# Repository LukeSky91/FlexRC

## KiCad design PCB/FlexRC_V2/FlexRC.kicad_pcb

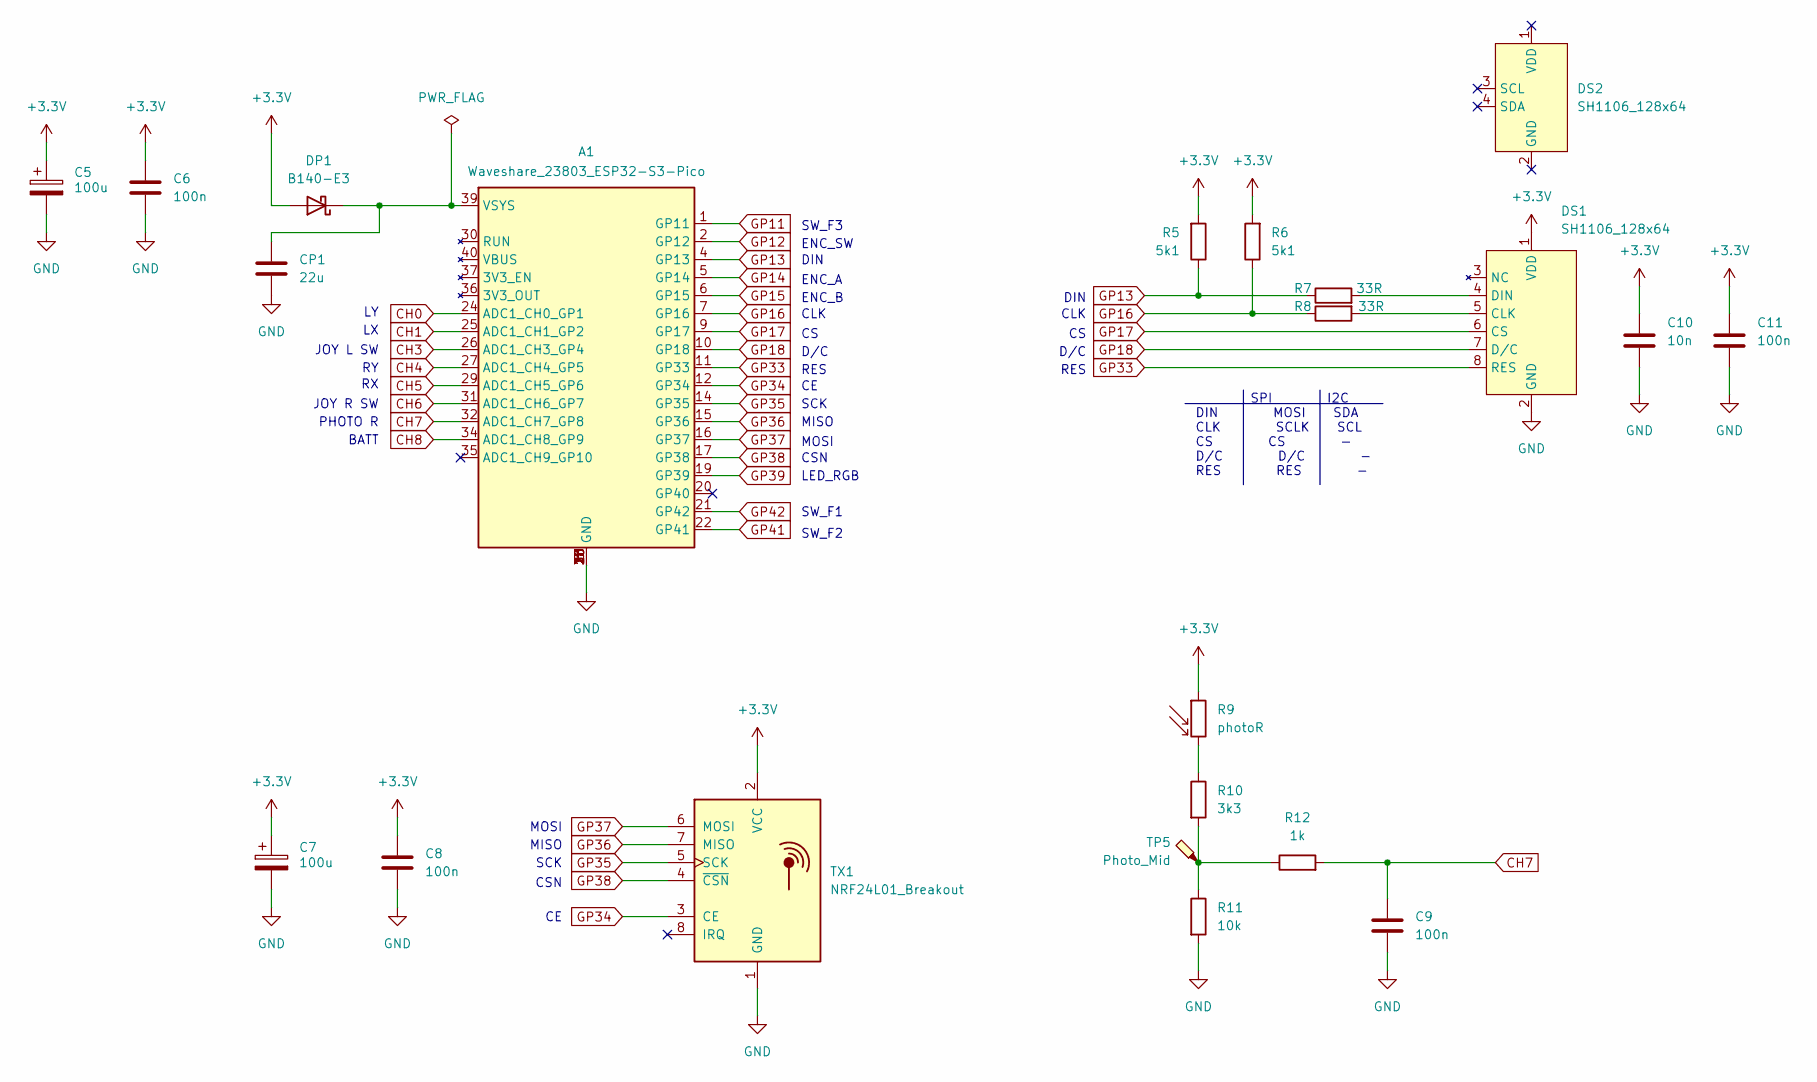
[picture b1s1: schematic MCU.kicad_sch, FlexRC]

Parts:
A1: Waveshare_23803_ESP32-S3-Pico
C5, C7: 100u; CP_Radial_Tantal_D6.0mm_P2.50mm
C6, C8, C9, C11: 100n; C_1206_3216Metric_Pad1.33x1.80mm_HandSolder
C10: 10n; C_1206_3216Metric_Pad1.33x1.80mm_HandSolder
CP1: 22u; C_1206_3216Metric_Pad1.33x1.80mm_HandSolder
DP1: B140-E3; D_SMA
DS1: SH1106_128x64; PinHeader_1x08_P2.54mm_Vertical
DS2: SH1106_128x64
R5, R6: 5k1; R_1206_3216Metric_Pad1.30x1.75mm_HandSolder
R7, R8: 33R; R_1206_3216Metric_Pad1.30x1.75mm_HandSolder
R9: photoR; photoResistor
R10: 3k3; R_1206_3216Metric_Pad1.30x1.75mm_HandSolder
R11: 10k; R_1206_3216Metric_Pad1.30x1.75mm_HandSolder
R12: 1k; R_1206_3216Metric_Pad1.30x1.75mm_HandSolder
TP5: Photo_Mid; TestPoint_Pad_D1.5mm
TX1: NRF24L01_Breakout; nRF24L01_Breakout

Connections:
+3.3V: C5.1, C6.1, C7.1, C8.1, C10.1, C11.1, DP1.2 (A), DS1.1 (VDD), R5.2, R6.2, R9.1, TX1.2 (VCC); also elsewhere on the board
CH0: A1.24 (ADC1_CH0_GP1); also elsewhere on the board
CH1: A1.25 (ADC1_CH1_GP2); also elsewhere on the board
CH3: A1.26 (ADC1_CH3_GP4); also elsewhere on the board
CH4: A1.27 (ADC1_CH4_GP5); also elsewhere on the board
CH5: A1.29 (ADC1_CH5_GP6); also elsewhere on the board
CH6: A1.31 (ADC1_CH6_GP7); also elsewhere on the board
CH7: A1.32 (ADC1_CH7_GP8), C9.1, R12.2
CH8: A1.34 (ADC1_CH8_GP9); also elsewhere on the board
GND: A1.3 (GND), A1.8 (GND), A1.13 (GND), A1.18 (GND), A1.23 (GND), A1.28 (GND), A1.33 (GND), A1.38 (GND), C5.2, C6.2, C7.2, C8.2, C9.2, C10.2, C11.2, CP1.2, DS1.2 (GND), R11.2, TX1.1 (GND); also elsewhere on the board
GP11: A1.1 (GP11); also elsewhere on the board
GP12: A1.2 (GP12); also elsewhere on the board
GP13: A1.4 (GP13), R5.1, R7.1
GP14: A1.5 (GP14); also elsewhere on the board
GP15: A1.6 (GP15); also elsewhere on the board
GP16: A1.7 (GP16), R6.1, R8.1
GP17: A1.9 (GP17), DS1.6 (CS)
GP18: A1.10 (GP18), DS1.7 (D/C)
GP33: A1.11 (GP33), DS1.8 (RES)
GP34: A1.12 (GP34), TX1.3 (CE)
GP35: A1.14 (GP35), TX1.5 (SCK)
GP36: A1.15 (GP36), TX1.7 (MISO)
GP37: A1.16 (GP37), TX1.6 (MOSI)
GP38: A1.17 (GP38), TX1.4 (~CSN)
GP39: A1.19 (GP39); also elsewhere on the board
GP41: A1.22 (GP41); also elsewhere on the board
GP42: A1.21 (GP42); also elsewhere on the board
unnamed: A1.39 (VSYS), CP1.1, DP1.1 (K)
unnamed: DS1.5 (CLK), R8.2
unnamed: DS1.4 (DIN), R7.2
unnamed: R9.2, R10.1
unnamed: R10.2, R11.1, R12.1, TP5.1 (1_1)

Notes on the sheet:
DIN
SCK
MISO
SPI I2C DIN MOSI SDA CLK SCLK SCL CS CS - D/C D/C - RES RES -
CLK
D/C
SW_F2
JOY L SW
ENC_B
MOSI
CSN
PHOTO R
RES
ENC_A
LED_RGB
JOY R SW
SW_F3
BATT
SW_F1
ENC_SW

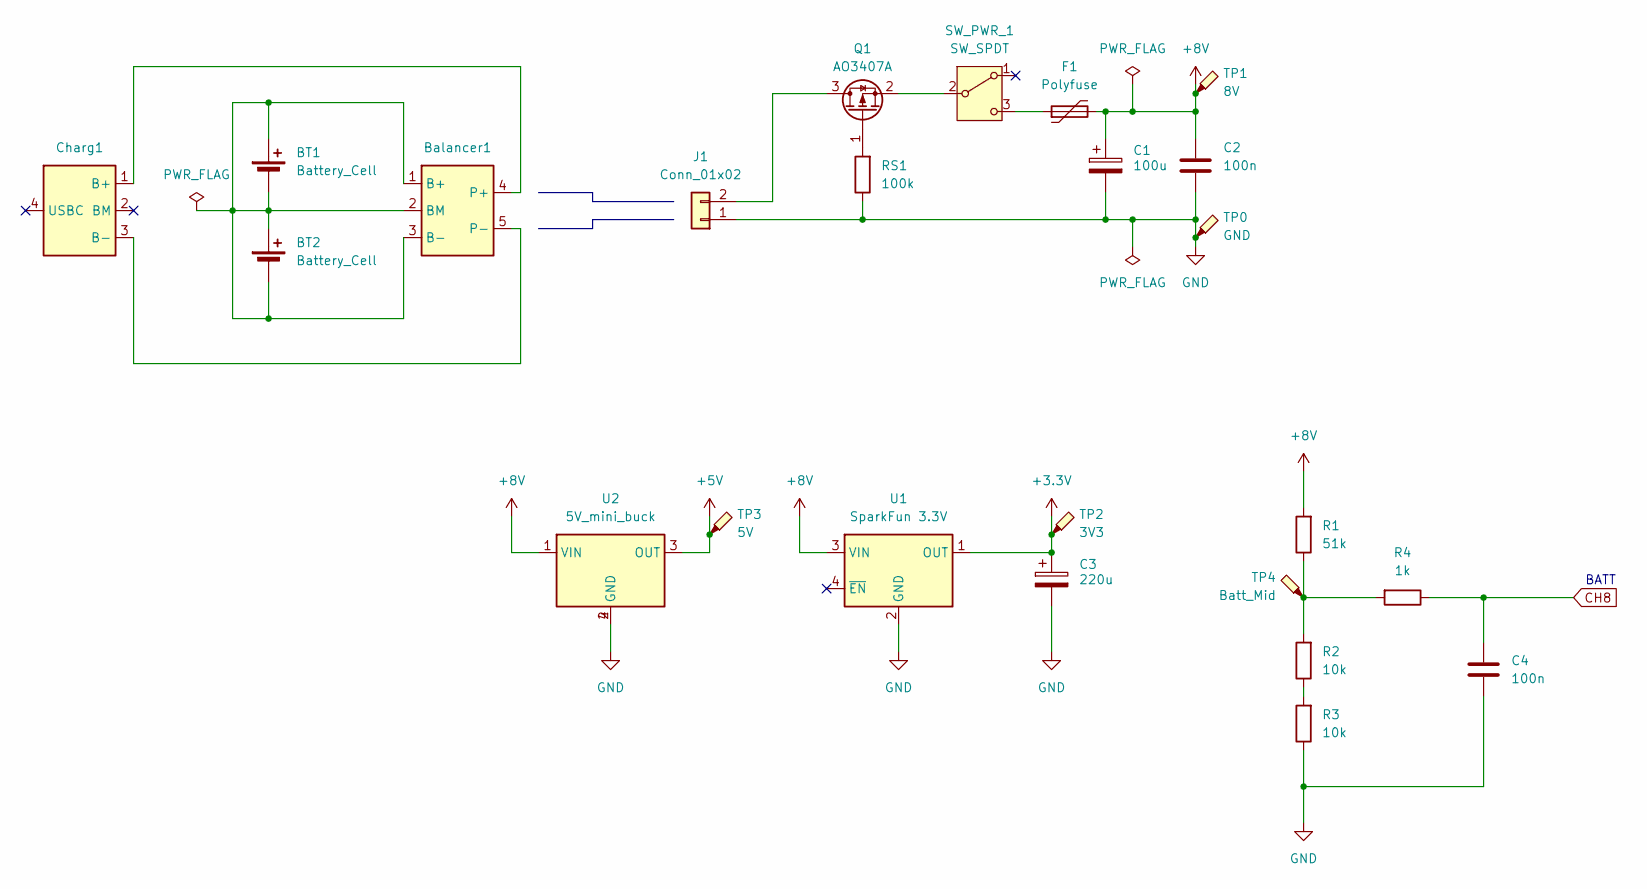
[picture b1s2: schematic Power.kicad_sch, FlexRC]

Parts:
BT1, BT2: Battery_Cell
Balancer1: Balancer
C1: 100u; CP_Radial_Tantal_D6.0mm_P2.50mm
C2, C4: 100n; C_Radial_D5.0mm_H5.0mm_P2.00mm
C3: 220u; CP_Radial_Tantal_D6.0mm_P2.50mm
Charg1: USB-C charger 2S
F1: Polyfuse; Fuse_Bourns_MF-RG300
J1: Conn_01x02; 2pin_header_new
Q1: AO3407A; SOT-23
R1: 51k; R_1206_3216Metric_Pad1.30x1.75mm_HandSolder
R2, R3: 10k; R_1206_3216Metric_Pad1.30x1.75mm_HandSolder
R4: 1k; R_1206_3216Metric_Pad1.30x1.75mm_HandSolder
RS1: 100k; R_1206_3216Metric_Pad1.30x1.75mm_HandSolder
SW_PWR_1: SW_SPDT; power_switch
TP0: GND; TestPoint_Pad_D1.5mm
TP1: 8V; TestPoint_Pad_D1.5mm
TP2: 3V3; TestPoint_Pad_D1.5mm
TP3: 5V; TestPoint_Pad_D1.5mm
TP4: Batt_Mid; TestPoint_Pad_D1.5mm
U1: SparkFun 3.3V; AP63203 step-down BabyBuck - 3,3V 2A - SparkFun COM-18357
U2: 5V_mini_buck

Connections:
+3.3V: C3.1, TP2.1 (1_1), U1.1 (OUT); also elsewhere on the board
+5V: TP3.1 (1_1), U2.3 (OUT); also elsewhere on the board
+8V: C1.1, C2.1, F1.2, R1.2, TP1.1 (1_1), U1.3 (VIN), U2.1 (VIN)
CH8: C4.1, R4.1; also elsewhere on the board
GND: C1.2, C2.2, C3.2, C4.2, J1.1, R3.1, RS1.1, TP0.1 (1_1), U1.2 (GND), U2.2 (GND), U2.4 (GND); also elsewhere on the board
unnamed: BT1.1 (+), BT1.2 (-), BT2.1 (+), BT2.2 (-), Balancer1.1 (B+), Balancer1.2 (BM), Balancer1.3 (B-)
unnamed: Balancer1.4 (P+), Charg1.1 (B+)
unnamed: Balancer1.5 (P-), Charg1.3 (B-)
unnamed: J1.2, Q1.3 (D)
unnamed: Q1.1 (G), RS1.2
unnamed: Q1.2 (S), SW_PWR_1.2 (B)
unnamed: R1.1, R2.2, R4.2, TP4.1 (1_1)
unnamed: R2.1, R3.2
unnamed: F1.1, SW_PWR_1.3 (C)

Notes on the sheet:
BATT

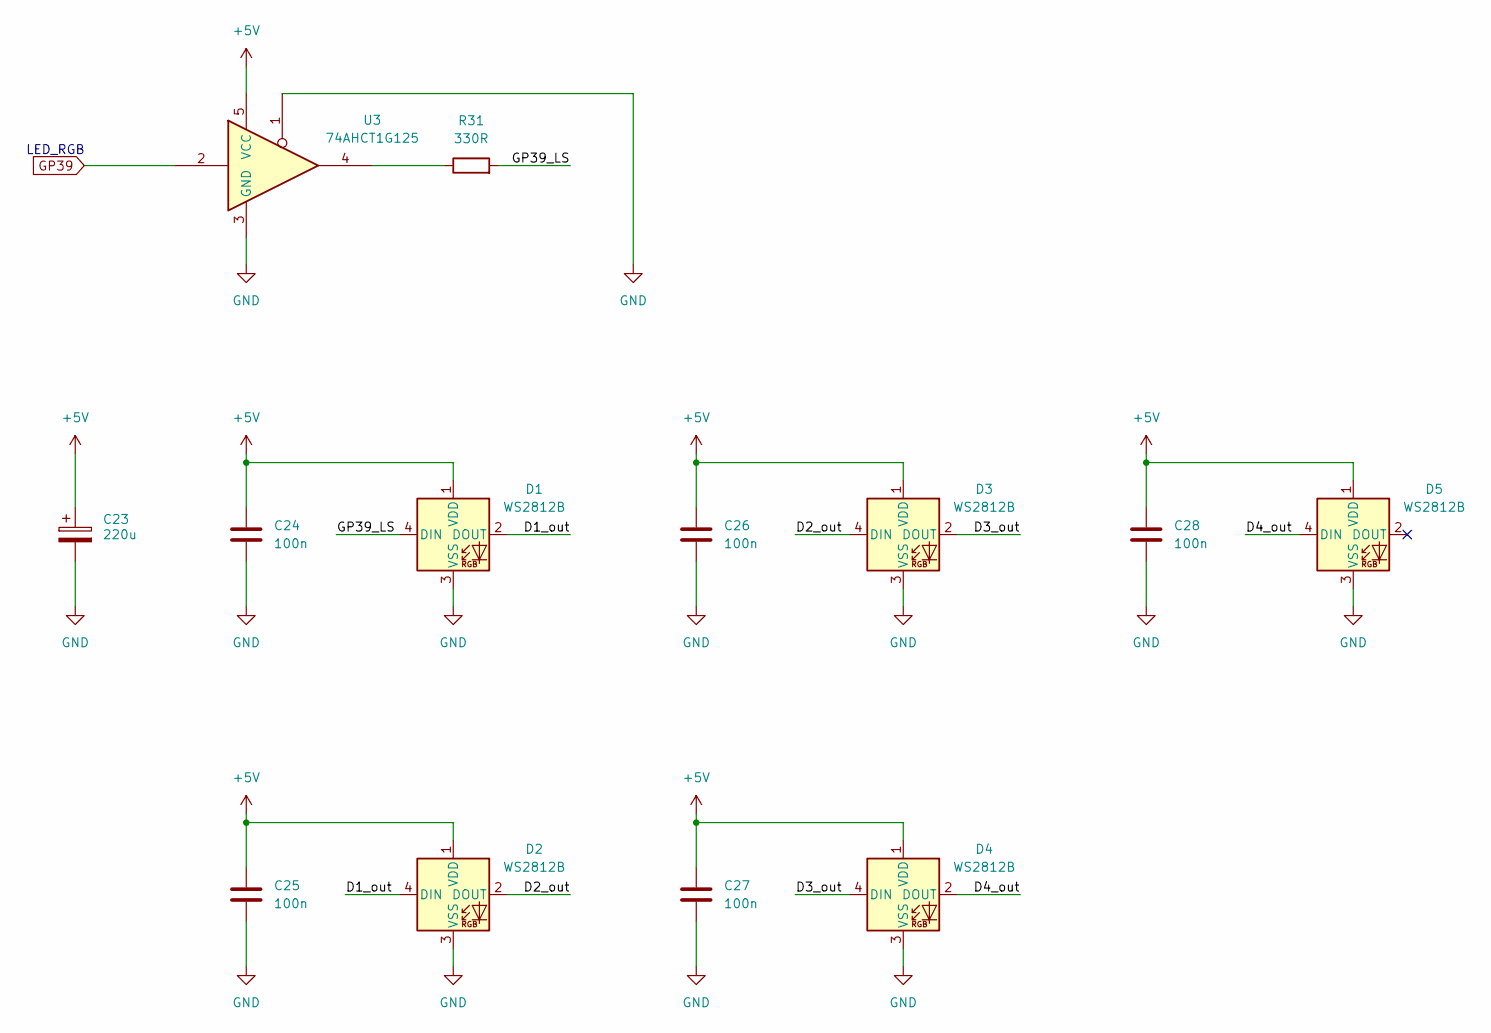
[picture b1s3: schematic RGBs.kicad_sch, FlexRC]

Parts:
C23: 220u; CP_Radial_Tantal_D6.0mm_P2.50mm
C24, C25, C26, C27, C28: 100n; C_1206_3216Metric_Pad1.33x1.80mm_HandSolder
D1, D2, D3, D4, D5: WS2812B; LED_WS2812B_PLCC4_5.0x5.0mm_P3.2mm
R31: 330R; R_1206_3216Metric_Pad1.30x1.75mm_HandSolder
U3: 74AHCT1G125; SOT-353_SC-70-5

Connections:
+5V: C23.1, C24.1, C25.1, C26.1, C27.1, C28.1, D1.1 (VDD), D2.1 (VDD), D3.1 (VDD), D4.1 (VDD), D5.1 (VDD), U3.5 (VCC); also elsewhere on the board
/RGBs/D1_out: D1.2 (DOUT), D2.4 (DIN)
/RGBs/D2_out: D2.2 (DOUT), D3.4 (DIN)
/RGBs/D3_out: D3.2 (DOUT), D4.4 (DIN)
/RGBs/D4_out: D4.2 (DOUT), D5.4 (DIN)
/RGBs/GP39_LS: D1.4 (DIN), R31.2
GND: C23.2, C24.2, C25.2, C26.2, C27.2, C28.2, D1.3 (VSS), D2.3 (VSS), D3.3 (VSS), D4.3 (VSS), D5.3 (VSS), U3.1, U3.3 (GND); also elsewhere on the board
GP39: U3.2; also elsewhere on the board
unnamed: R31.1, U3.4

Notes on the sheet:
LED_RGB

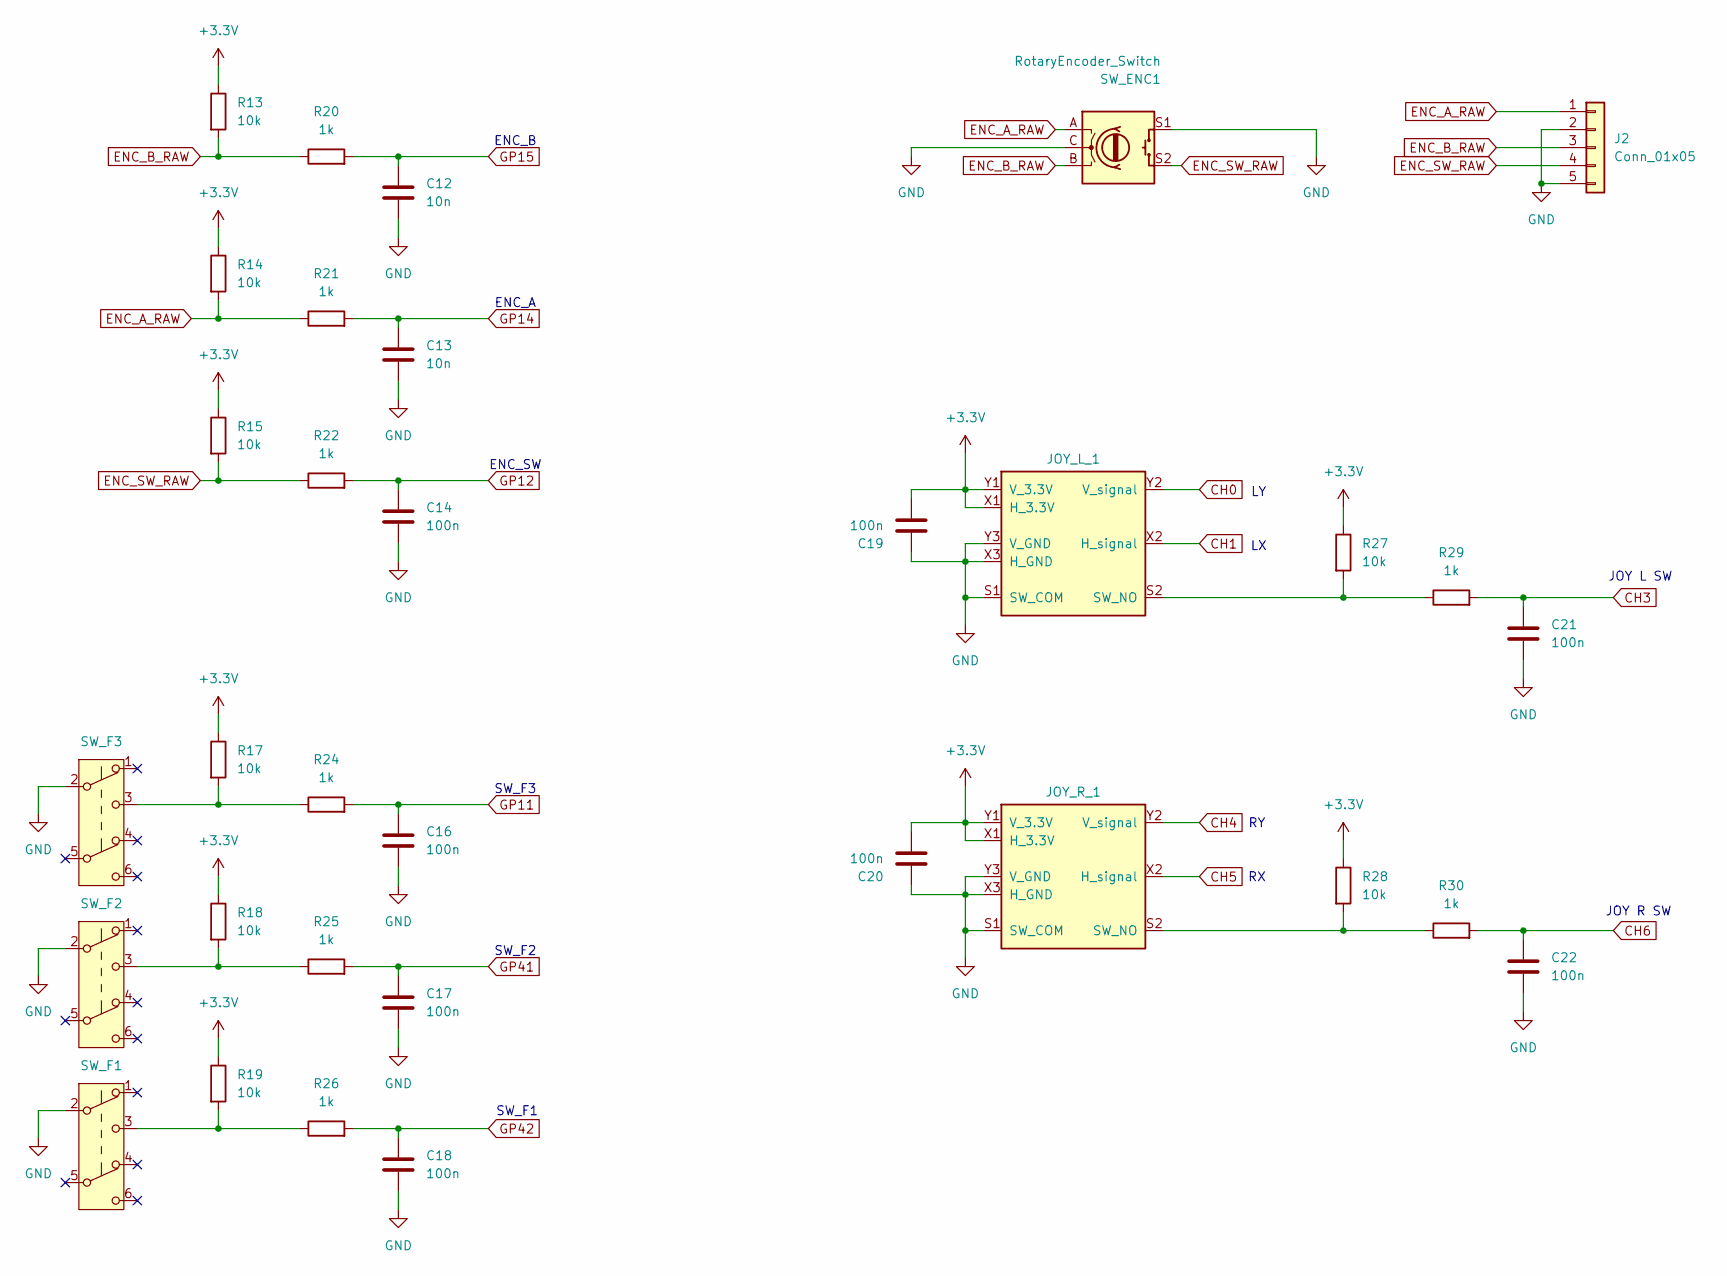
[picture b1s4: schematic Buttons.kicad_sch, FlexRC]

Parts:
C12, C13: 10n; C_1206_3216Metric_Pad1.33x1.80mm_HandSolder
C14, C16, C17, C18, C19, C20, C21, C22: 100n; C_1206_3216Metric_Pad1.33x1.80mm_HandSolder
J2: Conn_01x05; PinHeader_1x05_P2.54mm_Vertical
JOY_L_1: joystick-hall-effect; PS4_joystick
JOY_R_1: joystick-hall-effect; PS4_joystick
R13, R14, R15, R17, R18, R19, R27, R28: 10k; R_1206_3216Metric_Pad1.30x1.75mm_HandSolder
R20, R21, R22, R24, R25, R26, R29, R30: 1k; R_1206_3216Metric_Pad1.30x1.75mm_HandSolder
SW_ENC1: RotaryEncoder_Switch
SW_F1, SW_F2, SW_F3: PB07C; SW_PB07C_THT_6P

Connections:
+3.3V: C19.2, C20.2, JOY_L_1.X1 (H_3.3V), JOY_L_1.Y1 (V_3.3V), JOY_R_1.X1 (H_3.3V), JOY_R_1.Y1 (V_3.3V), R13.1, R14.1, R15.1, R17.1, R18.1, R19.1, R27.1, R28.1; also elsewhere on the board
CH0: JOY_L_1.Y2 (V_signal); also elsewhere on the board
CH1: JOY_L_1.X2 (H_signal); also elsewhere on the board
CH3: C21.1, R29.2; also elsewhere on the board
CH4: JOY_R_1.Y2 (V_signal); also elsewhere on the board
CH5: JOY_R_1.X2 (H_signal); also elsewhere on the board
CH6: C22.1, R30.2; also elsewhere on the board
ENC_A_RAW: J2.1, R14.2, R21.1, SW_ENC1.A
ENC_B_RAW: J2.3, R13.2, R20.1, SW_ENC1.B
ENC_SW_RAW: J2.4, R15.2, R22.1, SW_ENC1.S2
GND: C12.2, C13.2, C14.2, C16.2, C17.2, C18.2, C19.1, C20.1, C21.2, C22.2, J2.2, J2.5, JOY_L_1.S1 (SW_COM), JOY_L_1.X3 (H_GND), JOY_L_1.Y3 (V_GND), JOY_R_1.S1 (SW_COM), JOY_R_1.X3 (H_GND), JOY_R_1.Y3 (V_GND), SW_ENC1.C, SW_ENC1.S1, SW_F1.2 (B), SW_F2.2 (B), SW_F3.2 (B); also elsewhere on the board
GP11: C16.1, R24.2; also elsewhere on the board
GP12: C14.1, R22.2; also elsewhere on the board
GP14: C13.1, R21.2; also elsewhere on the board
GP15: C12.1, R20.2; also elsewhere on the board
GP41: C17.1, R25.2; also elsewhere on the board
GP42: C18.1, R26.2; also elsewhere on the board
unnamed: JOY_L_1.S2 (SW_NO), R27.2, R29.1
unnamed: JOY_R_1.S2 (SW_NO), R28.2, R30.1
unnamed: R17.2, R24.1, SW_F3.3 (C)
unnamed: R18.2, R25.1, SW_F2.3 (C)
unnamed: R19.2, R26.1, SW_F1.3 (C)

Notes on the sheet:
SW_F2
ENC_B
SW_F1
JOY L SW
ENC_A
JOY R SW
ENC_SW
SW_F3

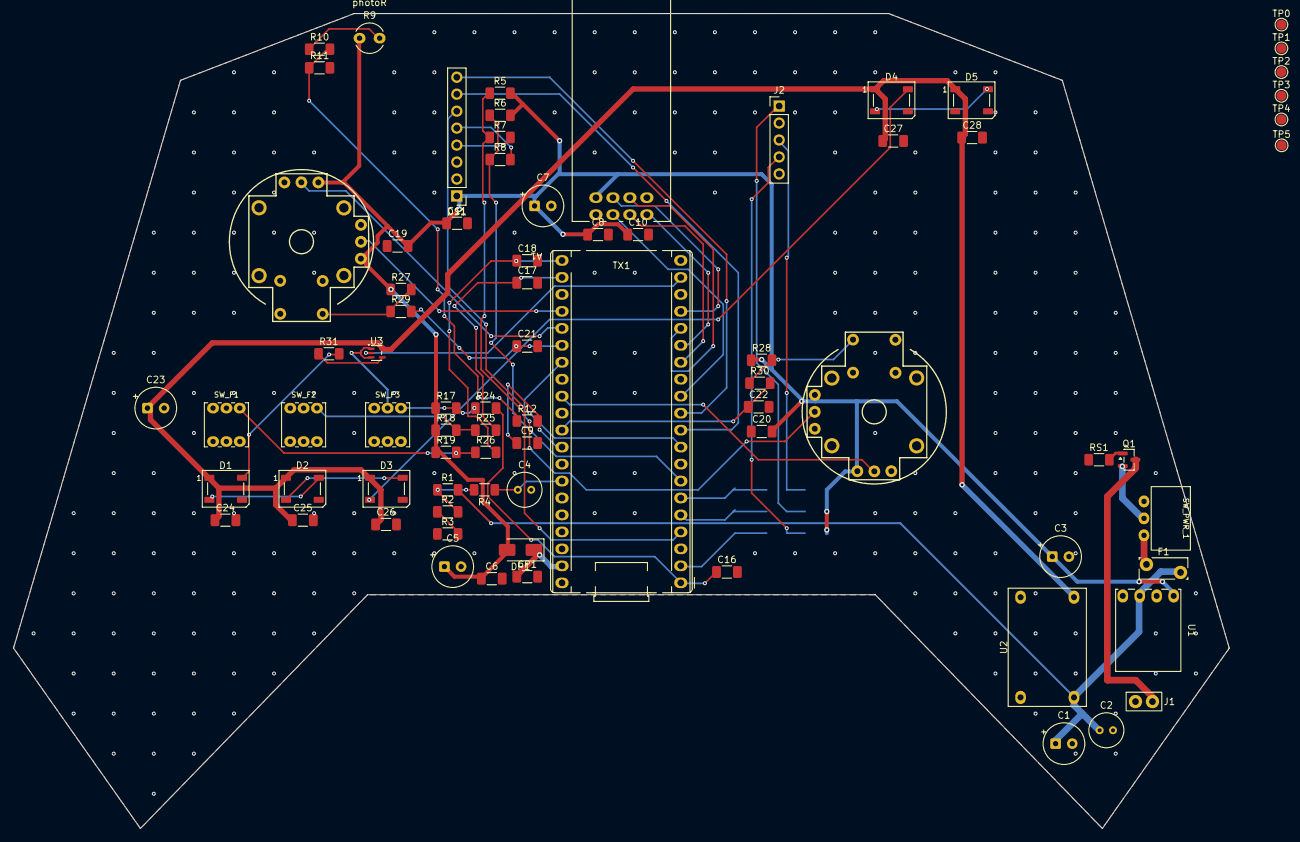
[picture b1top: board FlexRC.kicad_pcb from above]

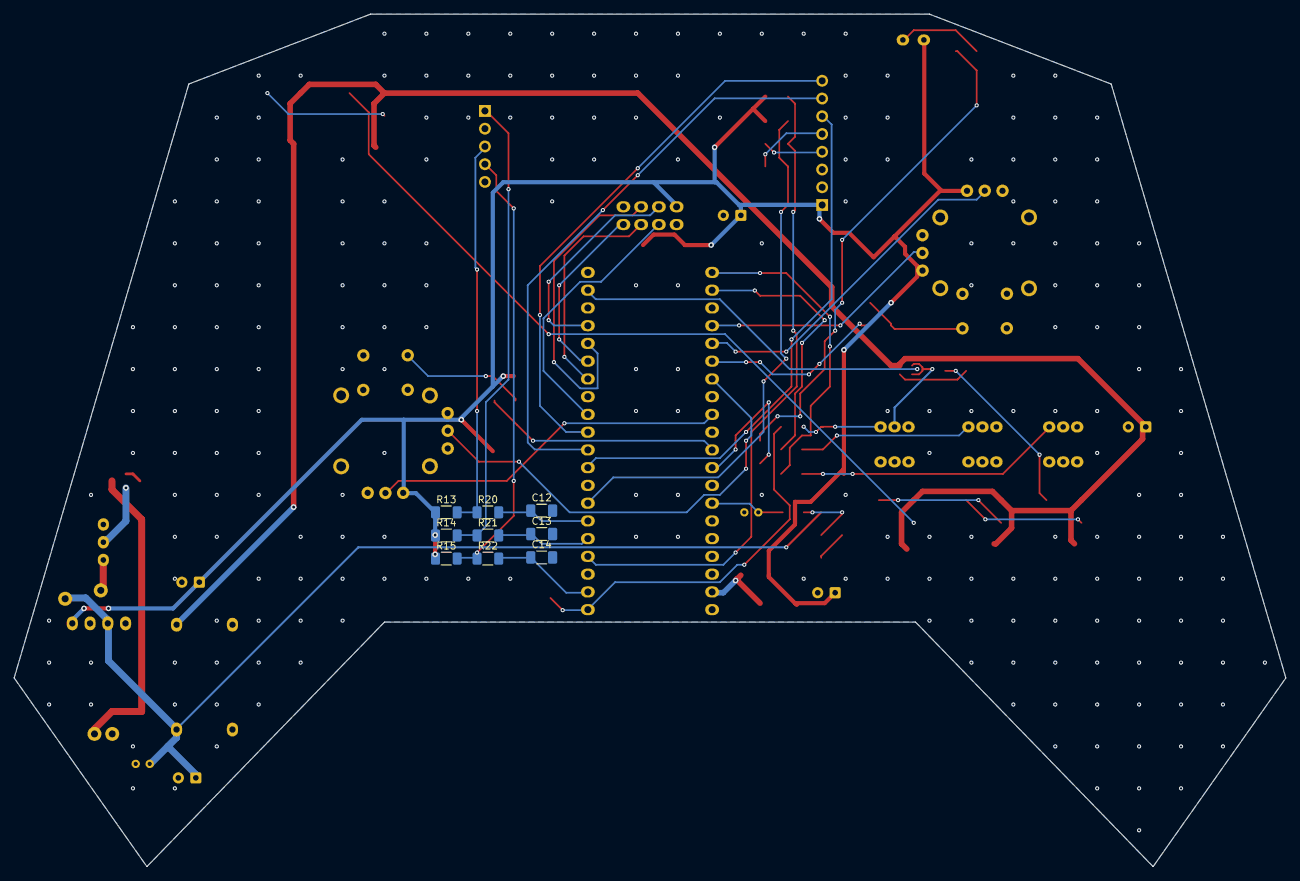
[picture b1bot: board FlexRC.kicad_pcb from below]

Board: 2 copper layers, 182.0 x 122.0 mm, 86 parts (9 on the bottom side), 54 nets.

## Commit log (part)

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2026-01-11 Initial commit – FlexRC_v1
2026-01-16 0116
2026-03-14 pico_v1
2026-03-15 FlexRC_esp32_v2
2026-03-16 FlexRC_esp32_v3
2026-03-17 FlexRC_esp32_v4
2026-03-25 esp32_v5
